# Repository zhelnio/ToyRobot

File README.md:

# ToyRobot
bluetooth crawler toy from 2014

**Video**

**Schematic**

**Board**

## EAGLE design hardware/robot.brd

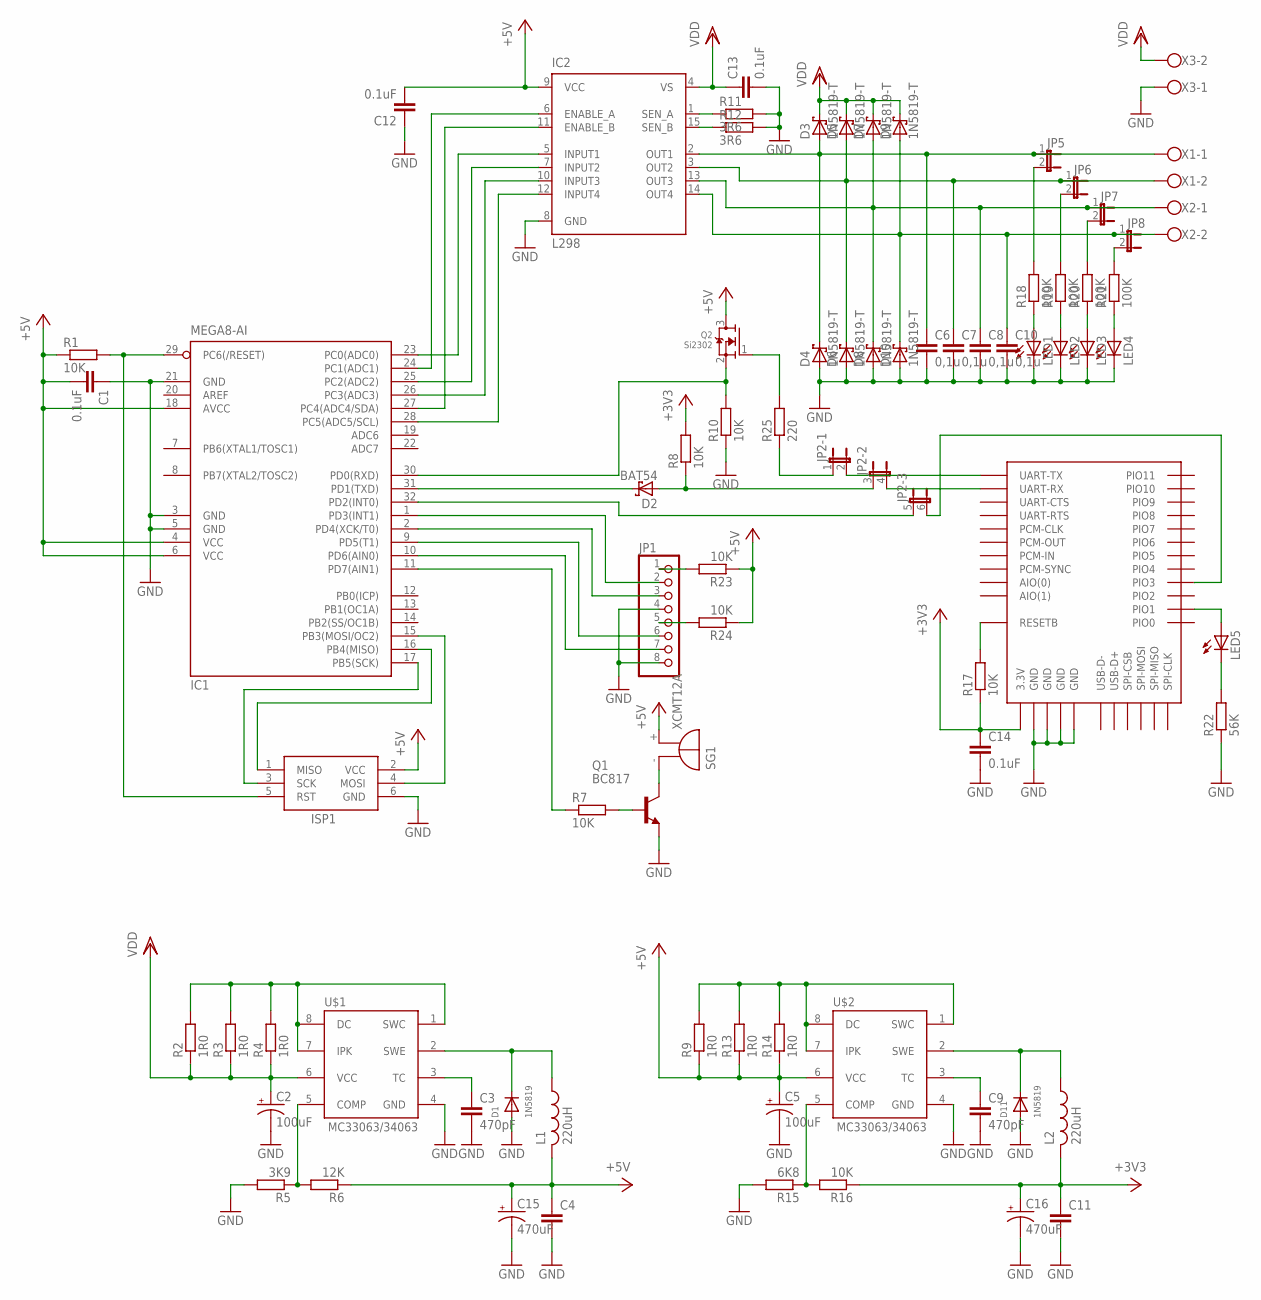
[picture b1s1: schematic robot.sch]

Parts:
C1, C12, C13, C14: 0.1uF; C1206K
C2, C5: 100uF; E2-5
C3, C9: 470pF; C1206K
C4, C11: C-EUC1206K; C1206K
C6, C7, C8, C10: 0,1u; C1206
C15, C16: 470uF; SANYO-OSCON_E13
D1, D11: 1N5819; SMADIODE
D2: BAT54; SOT23
D3, D4, D5, D6, D7, D8, D9, D10: 1N5819-T; DO41-7.6
IC1: MEGA8-AI; TQFP32-08
IC2: L298; MULTIWATT-15
ISP1: AVRISP-6; AVRISP
JP1: PINHD-1X8_2.54-90°; 1X08/90
JP2: JP3QE; JP3Q
JP5, JP6, JP7, JP8: JP1E; JP1
L1, L2: 220uH; 6000-XXXX-RC
LED1, LED2, LED3, LED4, LED5: LED3MM
Q1: BC817; SOT23-BEC
Q2: Si2302; SOT23
R1, R7, R8, R10, R16, R17, R23, R24: 10K; R1206
R2, R3, R4, R9, R13, R14: 1R0; R1206
R5: 3K9; R1206
R6: 12K; R1206
R11, R12: 3R6; R1206
R15: 6K8; R1206
R18, R19, R20, R21: 100K; R1206
R22: 56K; R1206
R25: 220; R1206
SG1: XCMT12A; F/QMBIII
U$1, U$2: MC33063/MC34063D; SO08
U$3: BTM400_6B; BTM400_6B_SIZE
X1, X2, X3: W237-102

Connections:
+3V3: C11.1, C14.1, C16.+, L2.2, R8.2, R16.1, R17.1, U$3.3.3V
+5V: C1.2, C4.1, C5.+, C12.2, C15.+, IC1.4 (VCC), IC1.6 (VCC), IC1.18 (AVCC), IC2.9 (VCC), ISP1.2 (VCC), L1.2, Q2.3 (D), R1.1, R6.1, R9.1, R13.1, R14.1, R23.1, R24.1, SG1.+ (-), U$2.6 (VCC)
GND: C1.1, C2.-, C3.2, C4.2, C5.-, C6.2, C7.2, C8.2, C9.2, C10.2, C11.2, C12.1, C13.2, C14.2, C15.-, C16.-, D1.A, D4.A, D6.A, D8.A, D10.A, D11.A, IC1.3 (GND), IC1.5 (GND), IC1.21 (GND), IC2.8 (GND), ISP1.6 (GND), JP1.4, JP1.8, LED1.K (C), LED2.K (C), LED3.K (C), LED4.K (C), Q1.E, R5.2, R10.1, R11.2, R12.2, R15.2, R22.1, U$1.4 (GND), U$2.4 (GND), U$3.GND@1 (GND), U$3.GND@2 (GND), U$3.GND@3 (GND), U$3.GND@4 (GND), X3.1
unnamed: IC2.1 (SEN_A), R11.1
unnamed: IC2.15 (SEN_B), R12.1
unnamed: C6.1, D3.A, D4.C, IC2.2 (OUT1), JP5.1, X1.1
unnamed: C7.1, D5.A, D6.C, IC2.3 (OUT2), JP6.1, X1.2
unnamed: JP5.2, R18.2
unnamed: C10.1, D9.A, D10.C, IC2.14 (OUT4), JP8.1, X2.2
unnamed: IC1.24 (PC1(ADC1)), IC2.6 (ENABLE_A)
unnamed: IC1.27 (PC4(ADC4/SDA)), IC2.11 (ENABLE_B)
unnamed: IC1.23 (PC0(ADC0)), IC2.5 (INPUT1)
unnamed: IC1.25 (PC2(ADC2)), IC2.7 (INPUT2)
unnamed: IC1.26 (PC3(ADC3)), IC2.10 (INPUT3)
unnamed: IC1.28 (PC5(ADC5/SCL)), IC2.12 (INPUT4)
unnamed: IC1.1 (PD3(INT1)), JP1.2
unnamed: IC1.2 (PD4(XCK/T0)), JP1.3
unnamed: IC1.9 (PD5(T1)), JP1.6
unnamed: IC1.10 (PD6(AIN0)), JP1.7
unnamed: Q1.C, SG1.- (+)
unnamed: Q1.B, R7.2
unnamed: R17.2, U$3.RESETB
unnamed: JP6.2, R19.2
unnamed: JP7.2, R20.2
unnamed: C8.1, D7.A, D8.C, IC2.13 (OUT3), JP7.1, X2.1
unnamed: JP8.2, R21.2
unnamed: LED1.A, R18.1
unnamed: LED2.A, R19.1
unnamed: LED3.A, R20.1
unnamed: LED4.A, R21.1
unnamed: D2.1 (A), JP2.3 (1), R8.1
unnamed: IC1.11 (PD7(AIN1)), R7.1
unnamed: R2.2, R3.2, R4.2, U$1.1 (SWC), U$1.7 (IPK), U$1.8 (DC)
unnamed: D1.C, L1.1, U$1.2 (SWE)
unnamed: R5.1, R6.2, U$1.5 (COMP)
unnamed: C3.1, U$1.3 (TC)
unnamed: LED5.K (C), R22.2
unnamed: D2.3 (C), IC1.31 (PD1(TXD))
unnamed: JP2.1, R25.1
unnamed: LED5.A, U$3.PIO(1) (PIO1)
unnamed: IC1.30 (PD0(RXD)), Q2.2 (S), R10.2
unnamed: IC1.29 (PC6(/RESET)), ISP1.5 (RST), R1.2
unnamed: IC1.15 (PB3(MOSI/OC2)), ISP1.4 (MOSI)
unnamed: IC1.16 (PB4(MISO)), ISP1.1 (MISO)
unnamed: IC1.17 (PB5(SCK)), ISP1.3 (SCK)
unnamed: JP2.6 (2), U$3.PIO(3) (PIO3)
unnamed: R9.2, R13.2, R14.2, U$2.1 (SWC), U$2.7 (IPK), U$2.8 (DC)
unnamed: R15.1, R16.2, U$2.5 (COMP)
unnamed: C9.1, U$2.3 (TC)
unnamed: D11.C, L2.1, U$2.2 (SWE)
unnamed: JP1.1, R23.2
unnamed: JP1.5, R24.2
unnamed: JP2.2, U$3.UART-TX
unnamed: JP2.4 (2), U$3.UART-RX
unnamed: IC1.32 (PD2(INT0)), JP2.5 (1)
unnamed: Q2.1 (G), R25.2
VDD: C2.+, C13.1, D3.C, D5.C, D7.C, D9.C, IC2.4 (VS), R2.1, R3.1, R4.1, U$1.6 (VCC), X3.2

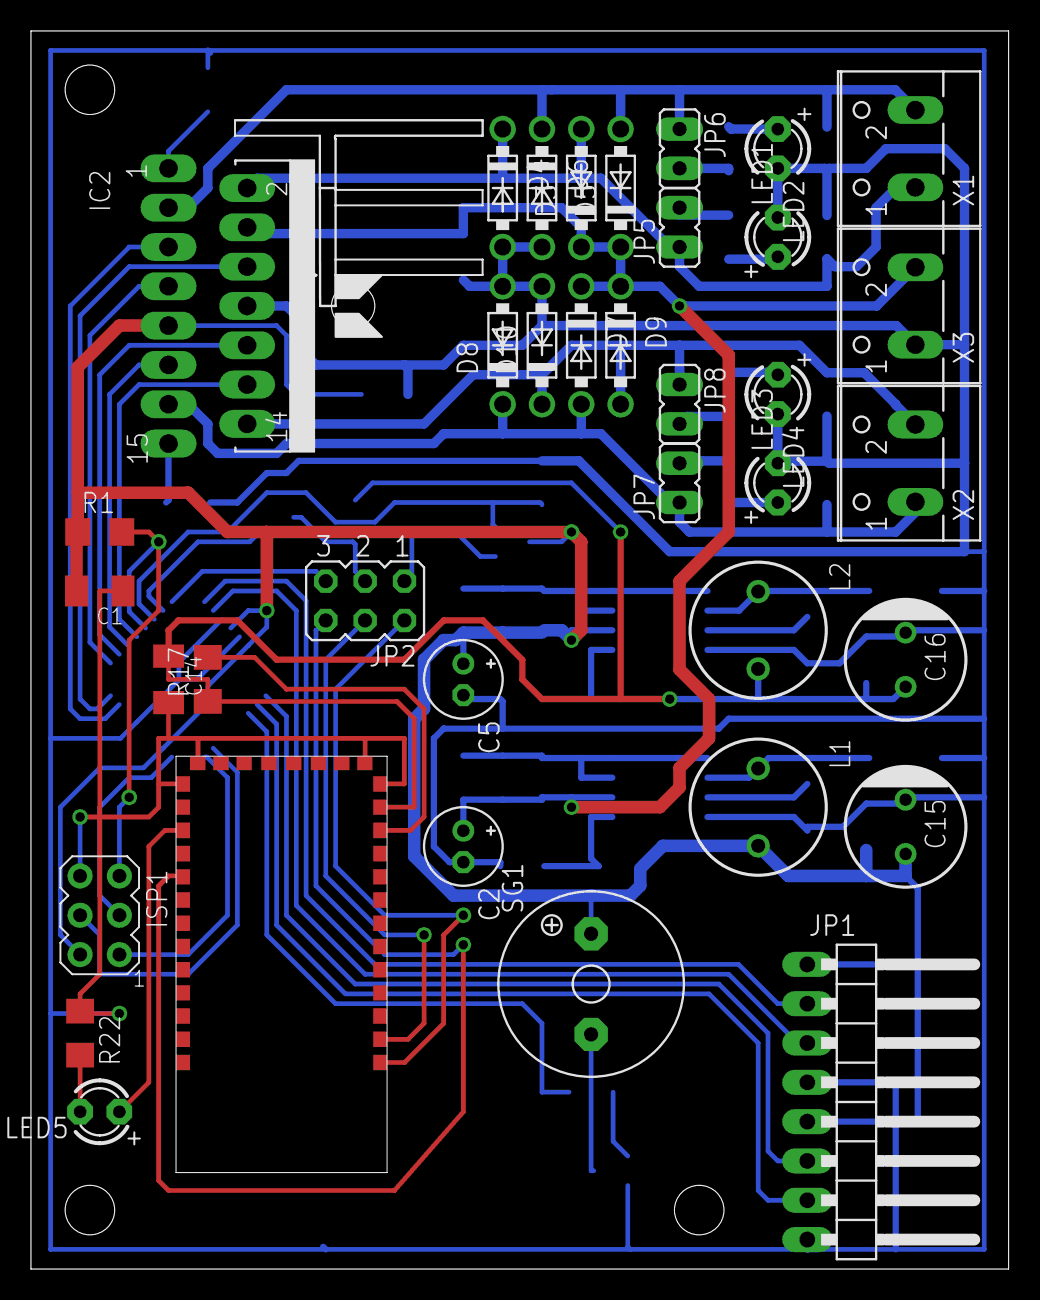
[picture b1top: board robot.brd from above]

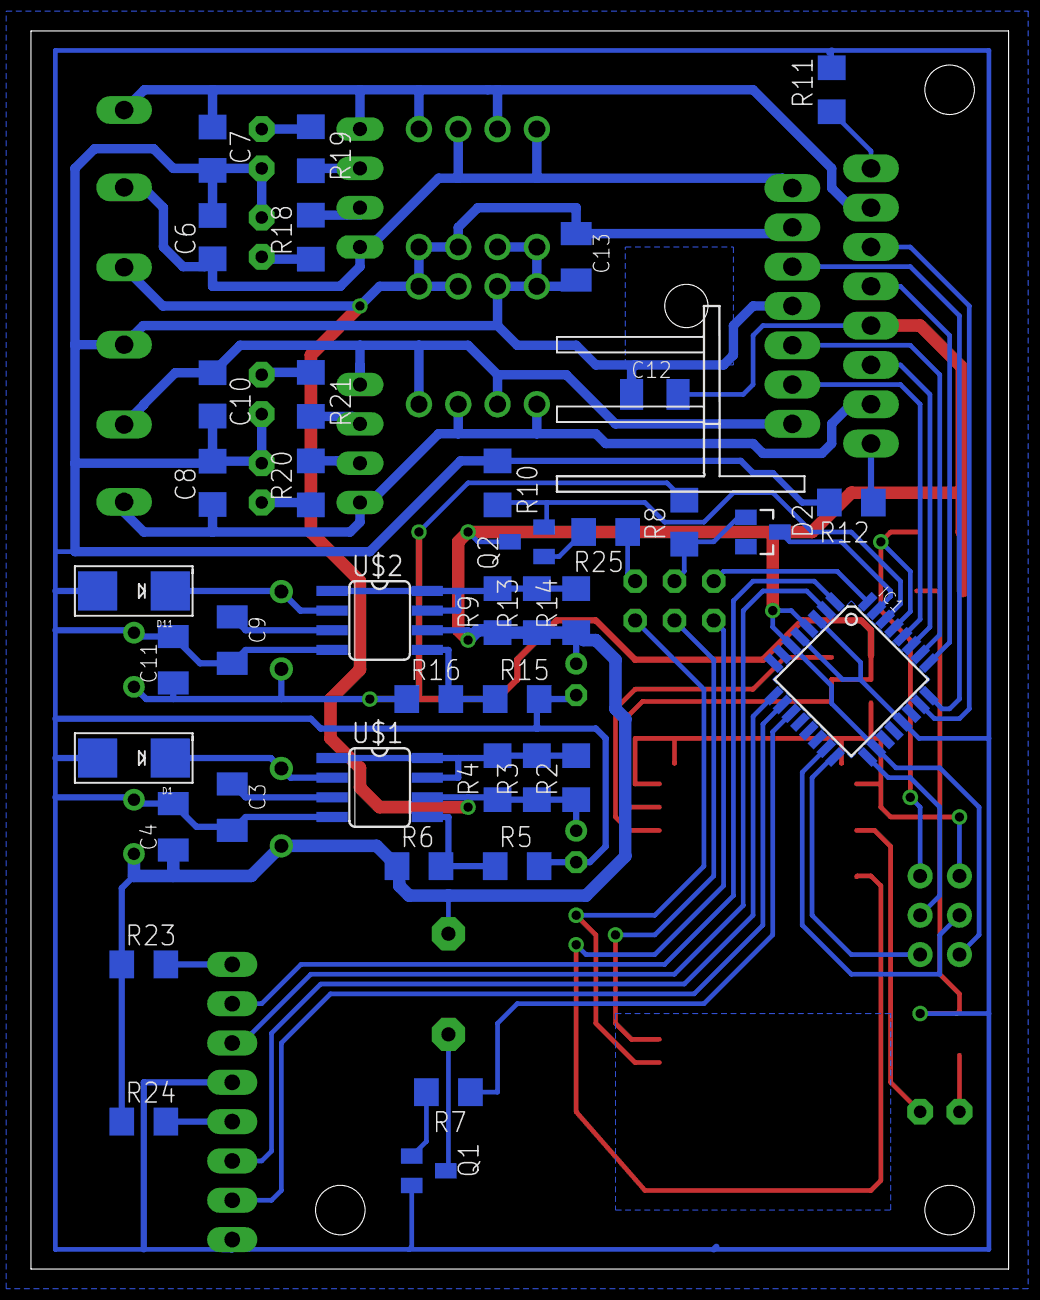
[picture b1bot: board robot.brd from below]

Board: 2 copper layers, 63.2 x 80.0 mm, 78 parts (40 on the bottom side), 57 nets.

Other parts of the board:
U$4: HS202-20

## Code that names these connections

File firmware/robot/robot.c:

/*
 * robot.c
 *
 * Created: 23.03.2014 16:35:55
 *  Author: stas
 */ 

#define	BAUDRATE	9600 // Скорость обмена данными
#define	F_CPU		1000000UL 

#include <avr/io.h>
#include <util/delay.h>
#include <avr/interrupt.h>
#include <stdlib.h>

#define A_PORT		PORTC
#define A_ENABLE	PORTC1
#define A_FORWARD	PORTC0
#define A_BACKWARD	PORTC2

#define B_PORT		PORTC
#define B_ENABLE	PORTC4
#define B_FORWARD	PORTC3
#define B_BACKWARD	PORTC5

#define S_PORT		PORTD
#define S_PIN		PORTD7

// Функция передачи данных по USART
void USART_Transmit( unsigned char data )
{
	while ( !( UCSR0A & (1<<UDRE0)) );	// Wait for empty transmit buffer
	UDR0 = data;						// Put data into buffer, sends the data
}

int main(void)
{
	/*
	конфигурация портов:
	двигатель А	PC1 - enable
				PC0 - input1
				PC2 - input2
				
	двигатель B	PC4 - enable
				PC3 - input3
				PC5 - input4
	
	оптрон А	PD3
				PD4
				
	оптрон B	PD5
				PD6
				
	пищалка		PD7
	*/
	
	//инициализируем порты
	
	//двигатель
	DDRC = 0;
	PORTC = (1 << A_ENABLE) | (1 << B_ENABLE);
	
	//пищалка
	DDRD &= ~(1 << DDD7);
	PORTD &= ~(1 << PORTD7);
	
	//таймер
	TCCR0A = 0;							// нормальный режим
	TCCR0B = (1 << CS00);				// без делителя (при 1МГц - каждые 0.256 мс)
	TIMSK0 = (1 << TOIE0);				// включить прерывания
	
	//usart
	
	UBRR0 = 12;								//задаем скорость (9600, по таблице, из расчета на множитель скорости)
	UCSR0A = (1 << U2X0);					//множитель скорости передачи (удвоить)
	UCSR0B = (1 << RXEN0) | (1 << TXEN0) | (1 << RXCIE0);	//разрешаем прием, передачу и прерывание по завершению приема
	UCSR0C = (1 << UCSZ00)| (1 << UCSZ01);	// асинхронный, без бита четности, 1 стоп, 8 бит передача, 
	
	/*
	UBRR0H = 0;								//задаем скорость (9600, по таблице, из расчета на множитель скорости)
	UBRR0L = 12;
	UCSR0A = (1 << U2X0);					//множитель скорости передачи (удвоить)
	UCSR0B = (1 << RXEN0) | (1 << TXEN0);
	UCSR0B |= (1 << RXCIE0);	//разрешаем прием, передачу и прерывание по завершению приема
	UCSR0C = (1 << UCSZ00)| (1 << UCSZ01);	// асинхронный, без бита четности, 1 стоп, 8 бит передача,
	*/
	
	USART_Transmit('O');	//Передаем при включении
	USART_Transmit('k');	//сообщение "Ok!", что свидетельствует
	USART_Transmit('!');	//о правильно работе программы
	
	//разрешить прерывания
	sei();
	
    while(1)
    {
		_delay_ms(1);	
    }
}

//глобальные переменные
volatile int16_t moveLeft = 0;
volatile int16_t moveRight = 0;
volatile uint16_t makeSound = 0;

inline void doLeftForward()
{
	A_PORT &= ~(1 << A_BACKWARD);
	A_PORT |= (1 << A_FORWARD);
}

inline void doLeftBackward()
{
	A_PORT &= ~(1 << A_FORWARD);
	A_PORT |= (1 << A_BACKWARD);
}

inline void doLeftStop()
{
	A_PORT &= ~(1 << A_FORWARD);
	A_PORT &= ~(1 << A_BACKWARD);
}

inline void doRightForward()
{
	B_PORT &= ~(1 << B_BACKWARD);
	B_PORT |= (1 << B_FORWARD);
}

inline void doRightBackward()
{
	B_PORT &= ~(1 << B_FORWARD);
	B_PORT |= (1 << B_BACKWARD);
}

inline void doRightStop()
{
	B_PORT &= ~(1 << B_FORWARD);
	B_PORT &= ~(1 << B_BACKWARD);
}

inline void doSound()
{
	uint8_t curState = S_PORT & (1 << S_PIN);
	if(curState > 0)
		S_PORT &= ~(1 << S_PIN);
	else
		S_PORT |= (1 << S_PIN);
}

inline void doSoundOff()
{
	S_PORT &= ~(1 << S_PIN);
}

//прерывание по завершению приема
ISR(USART_RX_vect)
{
	const uint16_t increment = 1000;
	const uint16_t limit = 1000;
	
	unsigned char data = UDR0;
	
	USART_Transmit(data);
		
	switch (data)
	{
		//вперед
		case 'w':
			if(moveLeft < limit)
				moveLeft += increment;
			if(moveRight < limit)
				moveRight += increment;
			break;
		
		//назад
		case 's':
			if(abs(moveLeft) < limit)
				moveLeft -= increment;
			if(abs(moveRight) < limit)
				moveRight -= increment;
			break;
		
		//влево
		case 'a':
			if(moveRight < limit)
				moveRight += increment;
			break;
		
		//вправо
		case 'd':
			if(moveLeft < limit)
				moveLeft += increment;
			break;
			
		//кручение влево
		case 'q':
			if(moveRight < limit)
				moveRight += increment;
			if(abs(moveLeft) < limit)
				moveLeft -= increment;
			break;
			
		//кручение вправо
		case 'e':	
			if(abs(moveRight) < limit)
				moveRight -= increment;	
			if(moveLeft < limit)
				moveLeft += increment;
			break;
			
		//пищалка
		case ' ':
			if(makeSound < 1000)
				makeSound += 1000;
			break;
			
		default:
			break;
	}
}

uint8_t test = 0;

//прерывание по таймеру
ISR(TIMER0_OVF_vect)
{
	//левая
	if(moveLeft > 0)
	{
		doLeftForward();
		moveLeft--;
	} 
	else if(moveLeft < 0)
	{
		doLeftBackward();
		moveLeft++;
	} 
	else
		doLeftStop();
	
	//правая
	if(moveRight > 0)
	{
		doRightForward();
		moveRight--;
	} 
	else if(moveRight < 0)
	{
		doRightBackward();
		moveRight++;
	} 
	else
		doRightStop();
		
	//пищалка
	if(makeSound > 0)
	{
		doSound();
		makeSound--;
	}
	else
		doSoundOff();
}

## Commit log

2017-06-30 :space_invader: Added .gitattributes & .gitignore files
2017-06-30 firmware
2017-06-30 hardware
2017-06-30 Create LICENSE
2017-06-30 Update LICENSE
2017-06-30 charset fix
